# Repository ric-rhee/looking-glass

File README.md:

# Looking Glass - Introduction
This is a smart mirror project for senior design at Purdue University\
The goal was to create a device that would save time in the morning by providing useful information on the mirror such as time, date, weather, notifications, news articles, etc.

## Features
1. Displays the time, date, and daily weather forecast
2. Activated either by walking in front of the device or pressing a button
3. Has a low power mode where the display dims and the sensors poll at a slower rate to save energy consumption

## System Design

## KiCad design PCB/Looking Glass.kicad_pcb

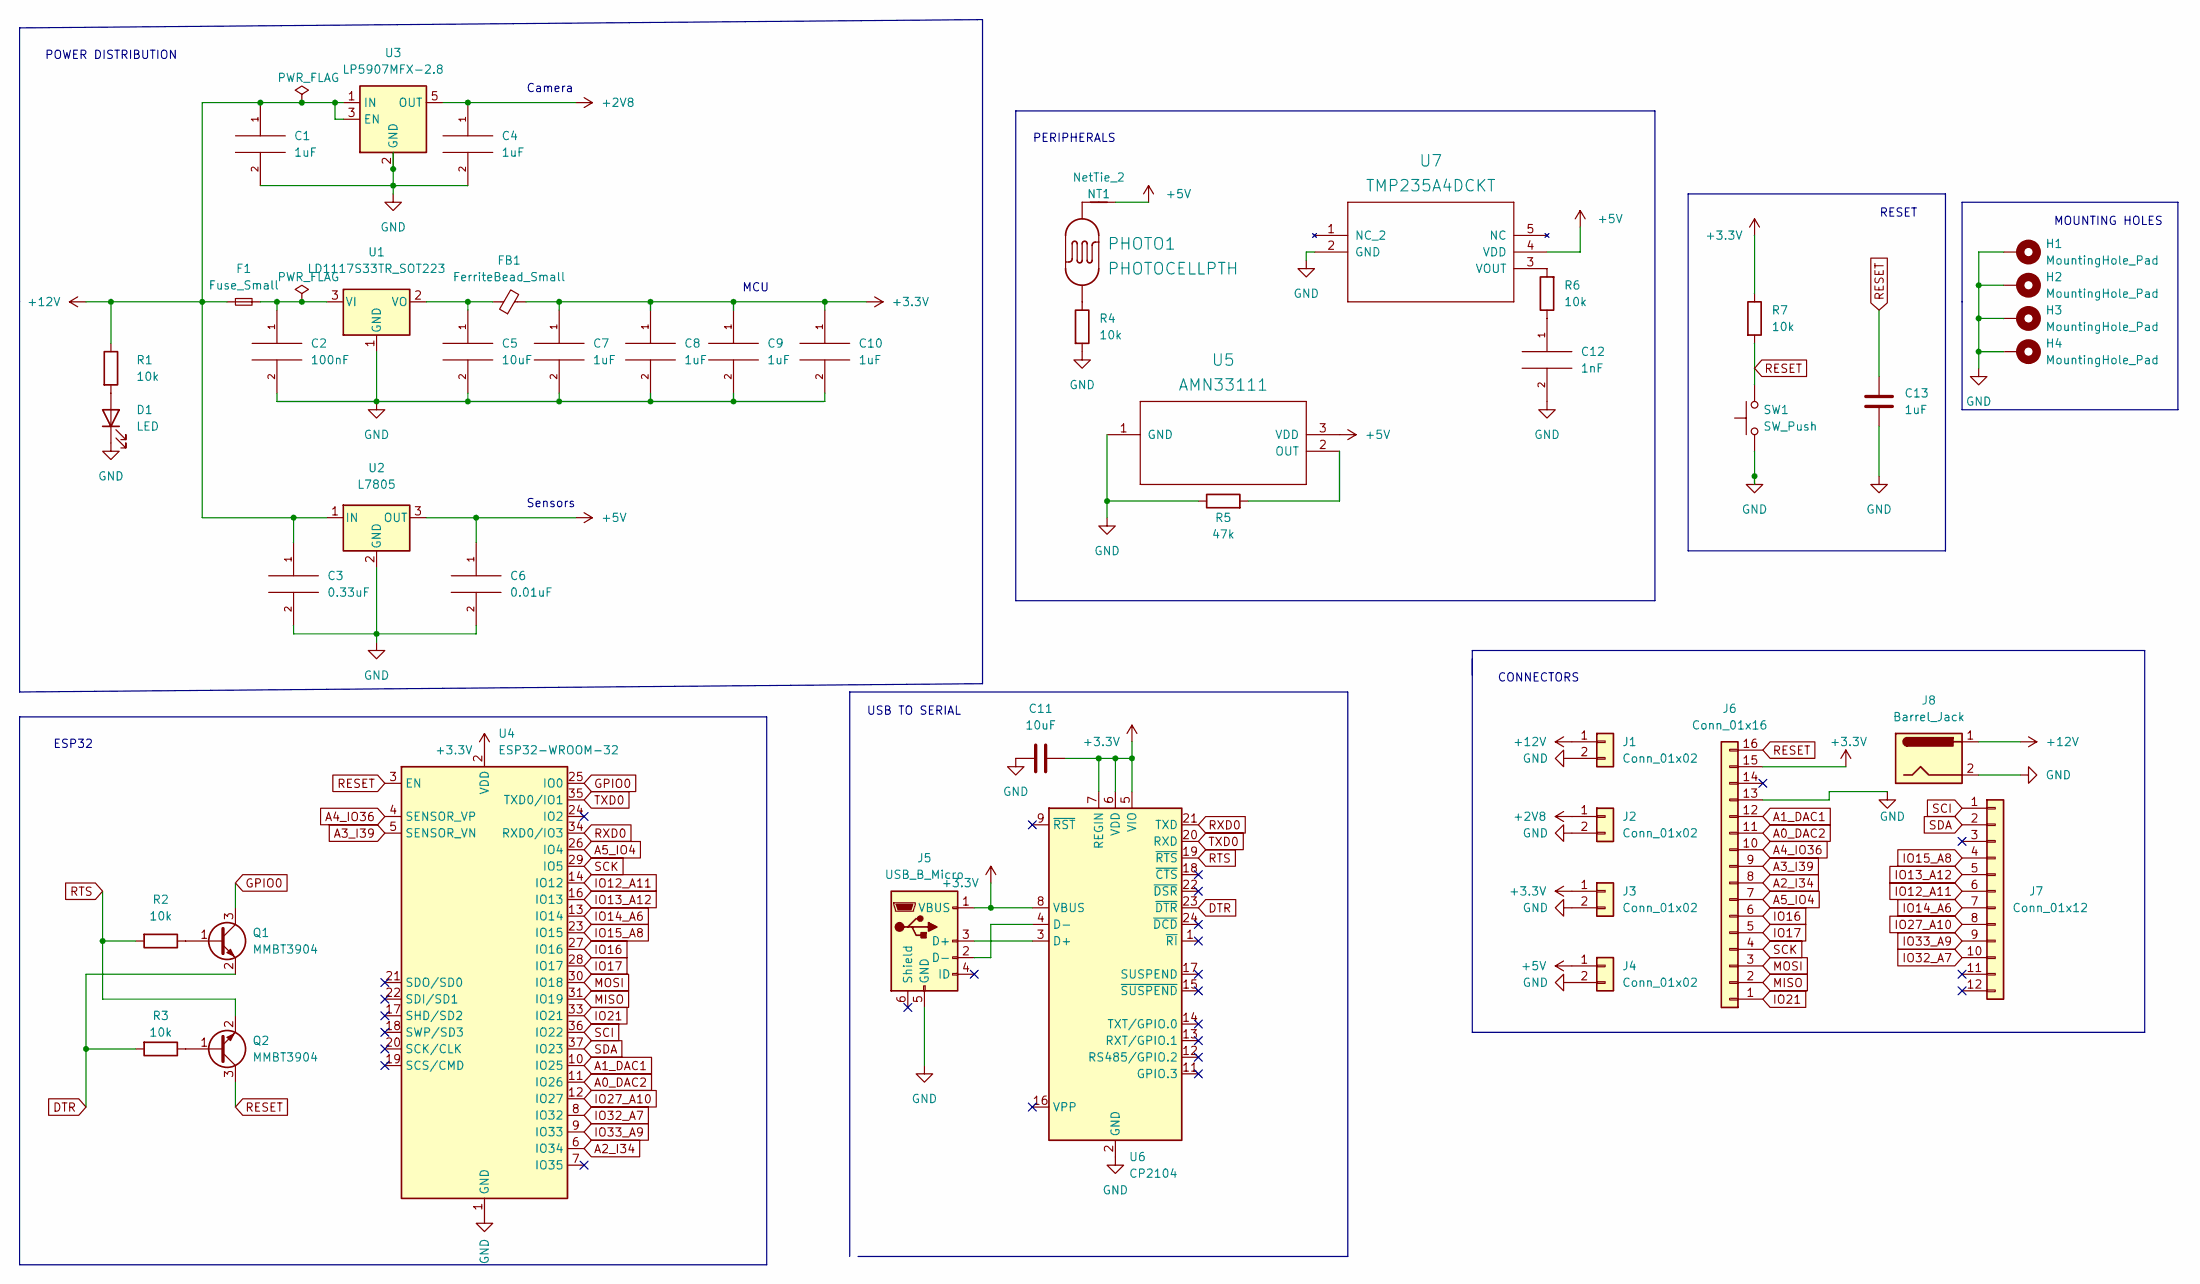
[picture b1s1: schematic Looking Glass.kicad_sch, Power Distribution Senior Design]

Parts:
C1, C4: 1uF; C_1206_3216Metric
C2: 100nF; C_0402_1005Metric
C3: 0.33uF; C_0603_1608Metric
C5, C11: 10uF; C_0805_2012Metric
C6: 0.01uF; C_01005_0402Metric
C7, C8, C9, C10, C13: 1uF; C_0805_2012Metric
C12: 1nF; C_01005_0402Metric
D1: LED; LED_D5.0mm
F1: Fuse_Small; Fuse_1206_3216Metric
FB1: FerriteBead_Small; L_0805_2012Metric
H1, H2, H3, H4: MountingHole_Pad; MountingHole_4.3mm_M4_Pad_Via
J1, J2, J3, J4: Conn_01x02; PinHeader_1x02_P2.54mm_Vertical
J5: USB_B_Micro; USB_Micro-B_Wuerth_629105150521
J6: Conn_01x16; PinHeader_1x16_P2.54mm_Vertical
J7: Conn_01x12; PinHeader_1x12_P2.54mm_Vertical
J8: Barrel_Jack; BarrelJack_Horizontal
NT1: NetTie_2; NetTie-2_SMD_Pad2.0mm
PHOTO1: PHOTOCELLPTH; PHOTOCELL-KIT
Q1, Q2: MMBT3904; SOT-23
R1: 10k; R_0201_0603Metric
R2, R3, R4, R6, R7: 10k; R_0402_1005Metric
R5: 47k; R_1206_3216Metric
SW1: SW_Push; SW_SPDT_PCM12
U1: LD1117S33TR_SOT223; SOT-223
U2: L7805; L7805CDT-TR
U3: LP5907MFX-2.8; SOT-23-5
U4: ESP32-WROOM-32
U5: AMN33111; AMN33111_PAN
U6: CP2104; QFN-24-1EP_4x4mm_P0.5mm_EP2.6x2.6mm
U7: TMP235A4DCKT; DCK5_TEX

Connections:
+2V8: C4.1, J2.1, U3.5 (OUT)
+3V3: C7.1, C8.1, C9.1, C10.1, C11.1, FB1.2, J3.1, J5.1 (VBUS), J6.15, R7.1, U4.2 (VDD), U6.5 (VIO), U6.6 (VDD), U6.7 (REGIN), U6.8 (VBUS)
+5V: C6.1, J4.1, NT1.2, U2.3 (OUT), U5.3 (VDD), U7.4 (VDD)
+12V: C1.1, C3.1, F1.1, J1.1, J8.1, R1.1, U2.1 (IN), U3.1 (IN), U3.3 (EN)
A0_DAC2: J6.11, U4.11 (IO26)
A1_DAC1: J6.12, U4.10 (IO25)
A2_I34: J6.8, U4.6 (IO34)
A3_I39: J6.9, U4.5 (SENSOR_VN)
A4_IO36: J6.10, U4.4 (SENSOR_VP)
A5_IO4: J6.7, U4.26 (IO4)
DTR: Q1.2 (E), R3.2, U6.23 (~DTR)
GND: C1.2, C2.2, C3.2, C4.2, C5.2, C6.2, C7.2, C8.2, C9.2, C10.2, C11.2, C12.2, C13.2, D1.1 (K), H1.1, H2.1, H3.1, H4.1, J1.2, J2.2, J3.2, J4.2, J5.5 (GND), J6.13, J8.2, R4.2, R5.1, SW1.1, U1.1 (GND), U2.2 (GND), U3.2 (GND), U4.1 (GND), U4.15 (GND), U4.38 (GND), U4.39 (GND), U5.1 (GND), U6.2 (GND), U6.25 (GND), U7.2 (GND)
GPIO0: Q1.3 (C), U4.25 (IO0)
IO12_A11: J7.6, U4.14 (IO12)
IO13_A12: J7.5, U4.16 (IO13)
IO14_A6: J7.7, U4.13 (IO14)
IO15_A8: J7.4, U4.23 (IO15)
IO16: J6.6, U4.27 (IO16)
IO17: J6.5, U4.28 (IO17)
IO21: J6.1, U4.33 (IO21)
IO27_A10: J7.8, U4.12 (IO27)
IO32_A7: J7.10, U4.8 (IO32)
IO33_A9: J7.9, U4.9 (IO33)
MISO: J6.2, U4.31 (IO19)
MOSI: J6.3, U4.30 (IO18)
unnamed: C2.1, F1.2, U1.3 (VI)
unnamed: C5.1, FB1.1, U1.2 (VO)
unnamed: C12.1, R6.1
unnamed: D1.2 (A), R1.2
unnamed: J5.2 (D-), U6.4 (D-)
unnamed: J5.3 (D+), U6.3 (D+)
unnamed: NT1.1, PHOTO1.2
unnamed: PHOTO1.1, R4.1
unnamed: Q1.1 (B), R2.1
unnamed: Q2.1 (B), R3.1
unnamed: R5.2, U5.2 (OUT)
unnamed: R6.2, U7.3 (VOUT)
RESET: C13.1, J6.16, Q2.3 (C), R7.2, SW1.2, U4.3 (EN)
RTS: Q2.2 (E), R2.2, U6.19 (~RTS)
RXD0: U4.34 (RXD0/IO3), U6.21 (TXD)
SCI: J7.1, U4.36 (IO22)
SCK: J6.4, U4.29 (IO5)
SDA: J7.2, U4.37 (IO23)
TXD0: U4.35 (TXD0/IO1), U6.20 (RXD)

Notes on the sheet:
RESET
POWER DISTRIBUTION
ESP32
PERIPHERALS
CONNECTORS
MCU
USB TO SERIAL
Sensors
Camera
MOUNTING HOLES

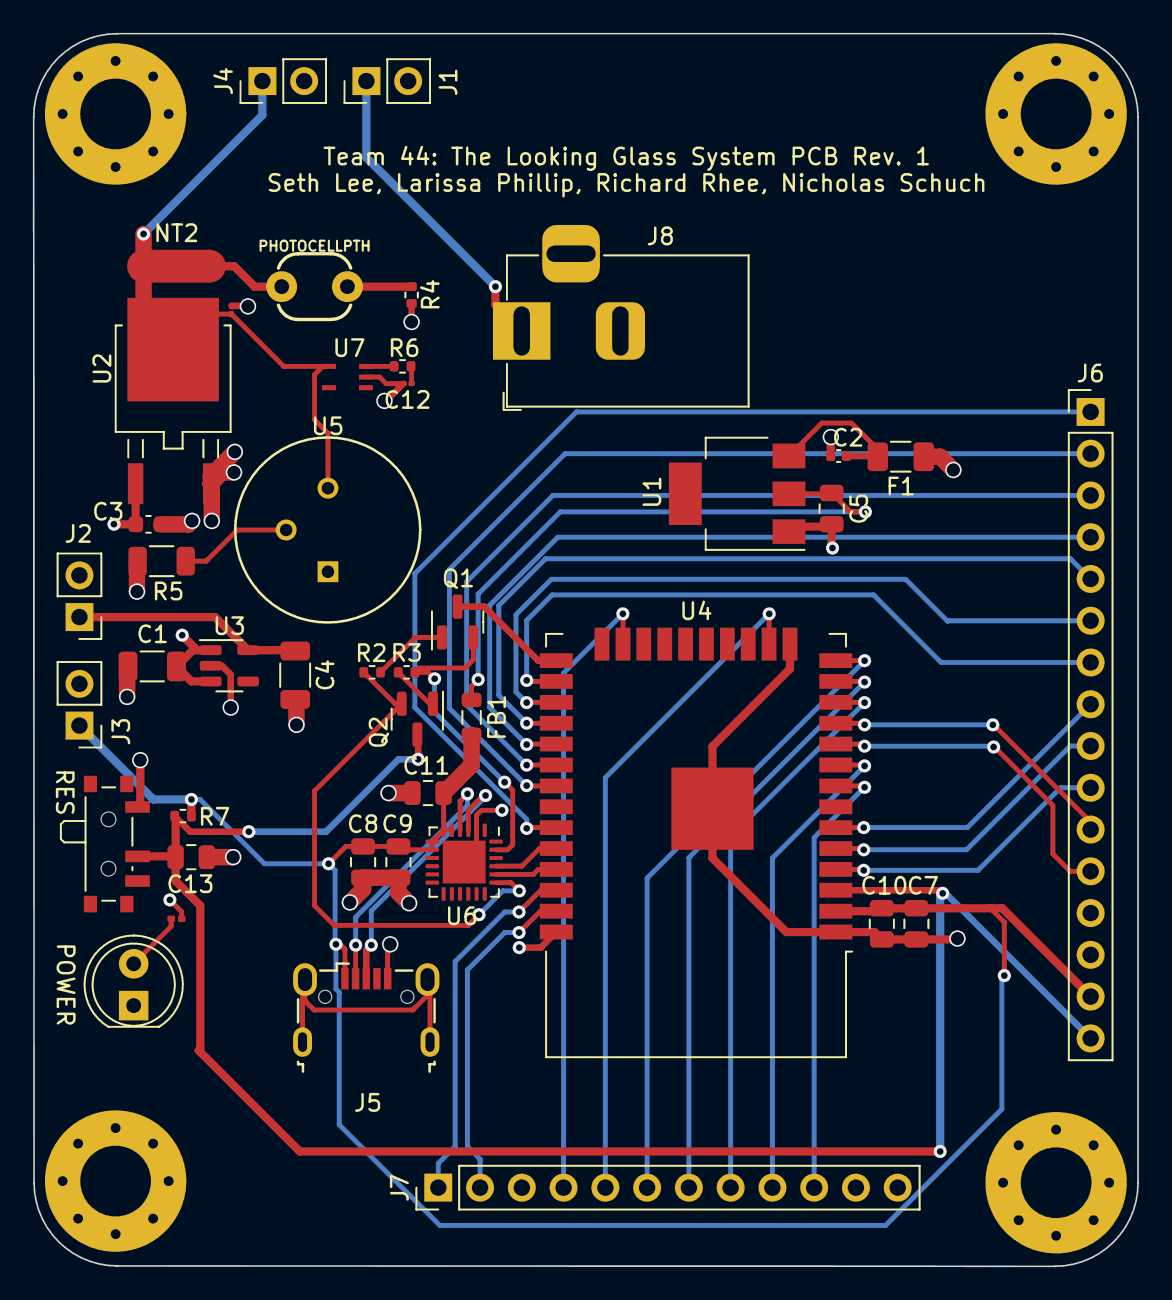
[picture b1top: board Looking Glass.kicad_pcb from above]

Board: 4 copper layers, 67.2 x 75.0 mm, 47 parts (0 on the bottom side), 44 nets.

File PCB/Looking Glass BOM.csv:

"Id";"Designator";"Package";"Quantity";"Designation";"Supplier and ref";
1;"F1";"Fuse_1206_3216Metric";1;"Fuse_Small";;;
2;"J8";"BarrelJack_Horizontal";1;"Barrel_Jack";;;
3;"J4,J3,J2,J1";"PinHeader_1x02_P2.54mm_Vertical";4;"Conn_01x02";;;
4;"U2";"L7805CDT-TR";1;"L7805";;;
5;"NT1";"NetTie-2_SMD_Pad2.0mm";1;"NT2";;;
6;"U6";"QFN-24-1EP_4x4mm_P0.5mm_EP2.6x2.6mm";1;"CP2104";;;
7;"R3,R6,R2,R4,R7";"R_0402_1005Metric";5;"10k";;;
8;"FB1";"L_0805_2012Metric";1;"FerriteBead_Small";;;
9;"U7";"DCK5_TEX";1;"TMP235A4DCKT";;;
10;"J5";"USB_Micro-B_Wuerth_629105150521";1;"USB_B_Micro";;;
11;"C8,C9,C13,C7,C10";"C_0805_2012Metric";5;"1uF";;;
12;"C6";"C_01005_0402Metric";1;"0.01uF";;;
13;"J7";"PinHeader_1x12_P2.54mm_Vertical";1;"Conn_01x12";;;
14;"SW1";"SW_SPDT_PCM12";1;"SW_Push";;;
15;"Q1,Q2";"SOT-23";2;"MMBT3904";;;
16;"U5";"AMN33111_PAN";1;"AMN33111";;;
17;"C3";"C_0603_1608Metric";1;"0.33uF";;;
18;"C12";"C_01005_0402Metric";1;"1nF";;;
19;"U3";"SOT-23-5";1;"LP5907MFX-2.8";;;
20;"U4";"ESP32-WROOM-32";1;"ESP32-WROOM-32";;;
21;"H1,H2,H3,H4";"MountingHole_4.3mm_M4_Pad_Via";4;"MountingHole_Pad";;;
22;"C11,C5";"C_0805_2012Metric";2;"10uF";;;
23;"J6";"PinHeader_1x16_P2.54mm_Vertical";1;"Conn_01x16";;;
24;"U1";"SOT-223";1;"LD1117S33TR_SOT223";;;
25;"R1";"R_0201_0603Metric";1;"10k";;;
26;"C4,C1";"C_1206_3216Metric";2;"1uF";;;
27;"R5";"R_1206_3216Metric";1;"47k";;;
28;"C2";"C_0402_1005Metric";1;"100nF";;;
29;"D1";"LED_D5.0mm";1;"LED";;;
30;"PHOTO1";"PHOTOCELL-KIT";1;"PHOTOCELLPTH";;;

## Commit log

2022-10-12 Add readme
2022-10-12 Add design doc pdf
2022-10-12 Update design doc
2022-10-12 Fix design doc
2023-10-24 Add reference picture of system in readme
2023-10-24 Add reference picture to readme
2023-10-24 Add reference image

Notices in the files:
parts and their libraries:
Copyright 2021 Accelerated Designs. All rights reserved.
